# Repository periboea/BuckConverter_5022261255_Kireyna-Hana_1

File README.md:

# protected lm2575 buck converter

all-tht adjustable step-down converter with three input protection stages.

## specs

- regulator: lm2575bt-adj (12 v input, 1.23 v to 10 v adjustable output via r1 3k and rv1 25k, plus sw1 on/off switch)
- overcurrent protection: ruef250 resettable ptc fuse (trips at 5 a)
- reverse polarity protection: fqp27p06 p-mosfet with 1n4744a 15 v zener diode and r4 10k resistor
- transient protection: 1.5ke27a tvs diode (clamps voltage spikes at 37.5 v, below the 40 v chip limit)
- pcb: 2-layer tht layout with 0.8 mm minimum trace width and 0 drc errors

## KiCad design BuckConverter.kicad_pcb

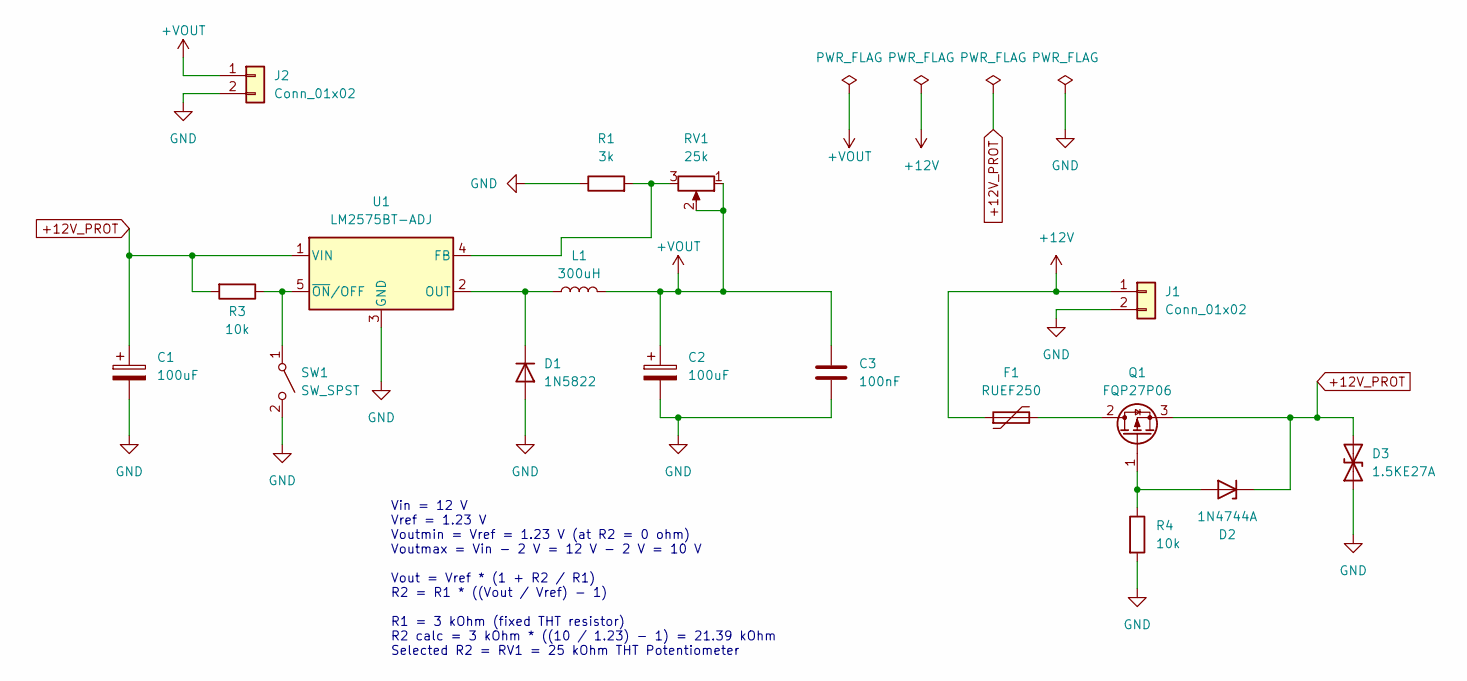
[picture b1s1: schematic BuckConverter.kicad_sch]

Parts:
C1, C2: 100uF; CP_Radial_D10.0mm_P7.50mm
C3: 100nF; C_Disc_D4.7mm_W2.5mm_P5.00mm
D1: 1N5822; D_DO-15_P15.24mm_Horizontal
D2: 1N4744A; D_DO-41_SOD81_P10.16mm_Horizontal
D3: 1.5KE27A; D_DO-201AD_P15.24mm_Horizontal
F1: RUEF250; Fuse_Bourns_MF-RG300
J1, J2: Conn_01x02; PinHeader_1x02_P2.54mm_Vertical
L1: 300uH; L_Radial_D13.5mm_P7.00mm_Fastron_09HCP
Q1: FQP27P06; TO-220-3_Vertical
R1: 3k; R_Axial_DIN0309_L9.0mm_D3.2mm_P12.70mm_Horizontal
R3, R4: 10k; R_Axial_DIN0309_L9.0mm_D3.2mm_P12.70mm_Horizontal
RV1: 25k; Potentiometer_ACP_CA9-V10_Vertical
SW1: SW_SPST; SW_SPST_Omron_B3F-40xx
U1: LM2575BT-ADJ; TO-220-5_Vertical

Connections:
+12V: F1.1, J1.1
+12V_PROT: C1.1, D2.1 (K), D3.2 (A2), Q1.3 (S), R3.2, U1.1 (VIN)
+VOUT: C2.1, C3.1, J2.1, L1.2, RV1.1, RV1.2
GND: C1.2, C2.2, C3.2, D1.2 (A), D3.1 (A1), J1.2, J2.2, R1.1, R4.2, SW1.2 (B), U1.3 (GND)
unnamed: D1.1 (K), L1.1, U1.2 (OUT)
unnamed: D2.2 (A), Q1.1 (G), R4.1
unnamed: F1.2, Q1.2 (D)
unnamed: R3.1, SW1.1 (A), U1.5 (~ON/OFF)
unnamed: R1.2, RV1.3, U1.4 (FB)

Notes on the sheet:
Vin = 12 V Vref = 1.23 V Voutmin = Vref = 1.23 V (at R2 = 0 ohm) Voutmax = Vin - 2 V = 12 V - 2 V = 10 V Vout = Vref * (1 + R2 / R1) R2 = R1 * ((Vout / Vref) - 1) R1 = 3 kOhm (fixed THT resistor) R2 calc = 3 kOhm * ((10 / 1.23) - 1) = 21.39 kOhm Selected R2 = RV1 = 25 kOhm THT Potentiometer

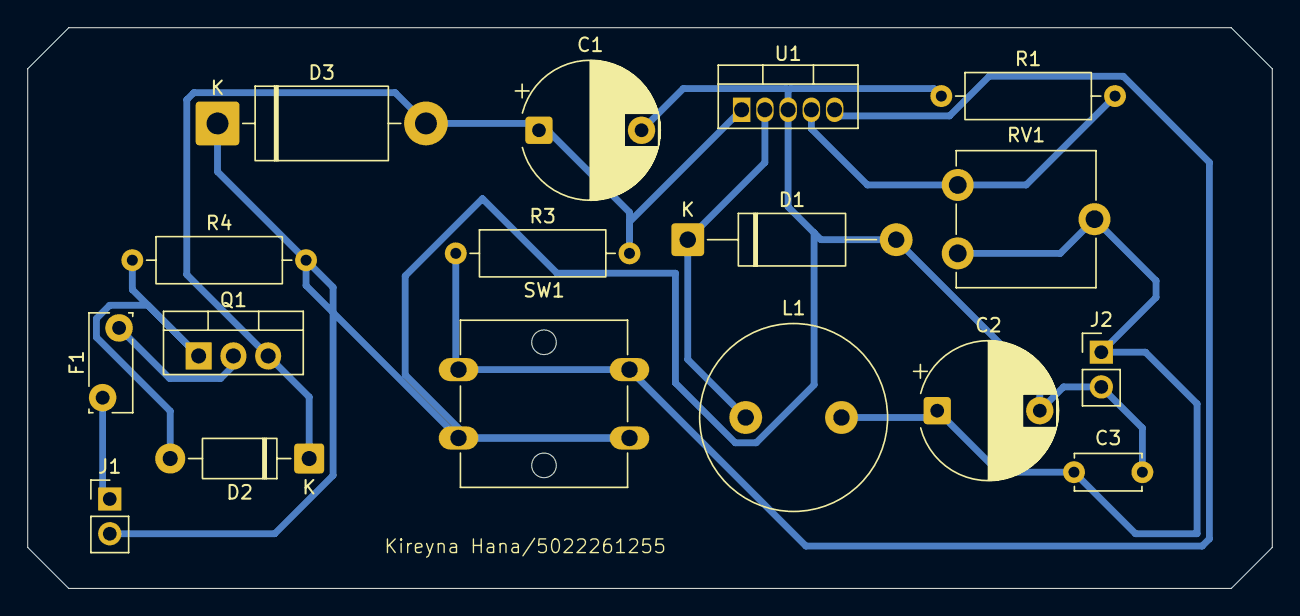
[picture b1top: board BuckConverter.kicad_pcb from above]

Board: 2 copper layers, 91.0 x 41.0 mm, 17 parts (0 on the bottom side), 9 nets.
